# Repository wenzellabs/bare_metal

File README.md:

# bare_metal

**bare metal** is an FPGA development board - the ideal platform to get started with FPGAs and HDL of one or another sort. all open source.

you can buy bare_metal <a href="https://lectronz.com/products/bare_metal"> over at my little lectronz shop</a>.

bare_metal, the opensource FPGA development board:

- five user buttons: OK, left, right, up, down
- large 16x8 SPI-addressable RGB LEDs display
- extensible through a PMOD interface
- comes with a battery for many hours of runtime
- extensive power management, monitoring and battery protection in HW
- allows for CPU-less designs or soft-core CPUs
- get into FPGAs with the **yosys** and **nextpnr** all open source toolchains
- program in python/amarant, verilog, spade or others
- comes with a stand
- three bright white LEDs as simple debug or flashlight
- usable as name tag, comes with a lace
- comes with a bootloader as 1st of four bitstreams
- can host up to 3 user bitstreams
- 16MBytes flash in total (1 bitstream takes < 128kBytes)
- 8MBytes RAM in total
- transputer research platform, as 3 user bitstreams can "boot" each other, see `bootloader` below
- hacky but feasible: more that 3 user bitstreams (hundreds)

## tech bits

### schematic

see the [hardware](hardware/) directory. find [the schematics](hardware/bare_metal_schematic.pdf), the KiCad sources and [some](hardware/bare_metal_front.png) [nice](hardware/bare_metal_back.png) [renderings](hardware/bare_metal_3d.png).

### memory

- 16MBytes SPI flash (W25Q128JVSIQ) this is where the FPGA boots from and user storage such as text, fonts, images, sounds, video, etc.
- 8MBytes SPI PSRAM (LY68L6400) far all of your extensive memory needs

here's a memory map of the SPI flash:

```
# 0x000_0000 - 0x000_009f =160b, multiboot header, slot table
# 0x000_00a0 - 0x001_efff ~124kB, slot 0, bare_metal_bootloader
# 0x001_f000 - 0x001_ffff =4kB, bootmetadata
# 0x002_0000 - 0x003_ffff =128kB, slot 1, user bitstream, hackerstacker_demo by default
# 0x004_0000 - 0x005_ffff =128kB, slot 2, another bitstream, transputers anyone?
# 0x006_0000 - 0x007_ffff ~128kB, slot 3, yab, hooray for transputers!
# 0x008_0000 - 0x100_0000 ~15.5MB, user data, images, fonts, text, sounds, videos etc
```
```
# in hackerstacker_demo, we reserve the first 512 KB for bootloader and bitstreams,
# and use the rest for user data:
# 0x008_0000 - 0x008_ffff = 64 kB, font data
# 0x009_0000 - 0x009_ffff = 64 kB, game data
# 0x00a_0000 - 0x00a_ffff = 64 kB, nick names
# 0x00b_0000 - 0x0ff_ffff = ~15.3MB images, video
```

### bootloader

the bootloader is always started after power up or reset. it lives in slot0 of the four default bitstream slots.

the bootloader is forked from https://github.com/tinyfpga/TinyFPGA-Bootloader which looks unmaintained nowadays. we forked, and implement our bootloader and the `tinyprog` flashing tool at https://codeberg.org/wenzellabs/bare_metal_bootloader

```

                   [-----------][----------][----------]
                   [ user bit- ][ user bit-][ user bit-]
                   [ stream 1  ][ stream 2 ][ stream 3 ]
                   [           ][          ][          ]
                   [===========][==========][==========]
                   [-----------------------------------]
                   [    USB-bootloader bitstream 0     ]
                   [===================================]
               [-------------------------------------------]
               [ iCE40-up5k-sg48 FPGA, 5k LCs, DSP fn()s   ]
               [===========================================]
[-----]    [----------------------------------------------------]    [---------------]
[ USB ]----[ bare_metal, buttons, batt., LEDs, RGB-display, PMOD]----[PMOD extensions]
[=====]    [====================================================]    [===============]

```

the bootloader animates the three white LEDs `index`, `middle` and `pinky`. if the bootloader detects a host PC (if it gets USB enumerated) it stays in the bootloader and creates a cdc_acm /dev/ttyACM0 that can be used in conjunction with tinyprog to flash user bitstreams into slot1, slot2 or slot3, or any other flash content.

if no host PC is detected the bootloader "jumps" to the user bitstream in slot1.

**stay in bootloader** although there's no host PC:

- press btn_**down** while powerup/reset.

jump to **slot1** user bitstrem although we're connected to a host PC:

- press btn_**ok** while powerup/reset.

jump to **slot2** user bitstrem although we're connected to a host PC:

- press btn_**left** while powerup/reset.

jump to **slot3** user bitstrem although we're connected to a host PC:

- press btn_**right** while powerup/reset.

### examples

#### hackerstacker_demo

by default the first user bitstream in slot1 is hackerstacker_demo, that has various modes, which can be advanced by a long btn_ok press.

modes:

- hackerstacker game, control: btn_ok
- scroll user text. control: switch text: btn_ok, brightness: btn_up, btn_down, scroll-mode: btn_left, font: btn-right
- skating images. control: btn_ok
- various static patterns, rainbow, trans flag, checker board. control: btn_ok
- various animated patterns, rainbow, trans flag. control: btn_ok

the texts, fonts and images live in the SPI flash aside from the bitstream, so they can be replaced or extended without re-synthesizing the bitstream.
see [the hackerstacker_demo directory](firmware/examples/amaranth/hackerstacker_demo) and there the make targets
```
make flash-nick # see nick.txt first!
make flash-font
make flash-image # see image.txt first!
```

#### julia

reach it by pressing btn_left while powerup/reset.

by default the second user bitstream in slot2 is julia. it renders a julia set, and loops:

- pan to a random position
- zoom in until the entropy is too low
- zoom out again

the up/down/left/right control the complex coordinate C of the julia set being rendered.

the OK button changes the palette.

#### psram_probe

reach it by pressing btn_right while powerup/reset.

for now the default third user bitstream in slot3 is psram_probe, just a production PSRAM test. lights up one LED in green per pass.

I hope to get some small spade demo, looking at you @TheZoq2.

### power

#### battery

a PS5 controller compatible battery similar to SNYHR37. 2500 mAh, 1S.
the little plasic box is a nice feature to protect the pouch cell from stabbing you and vice versa.

#### USB-C

there's a current limit of 500mA in place. no USB-PD, just 5V.

the data pins are usable and available for creating any USB2 devices. the board has no dedicated USB-HW (aside from ESD protection) but anything can be implemented in the FPGA, just as the bootloader does. related pins:

```
# USB
set_io -nowarn usbp         42    # IOT_51a  - USB D+
set_io -nowarn usbn         38    # IOT_50b  - USB D-
set_io -nowarn usb_det      37    # IOT_36b  - USB_DET, active-high enables 1k5 pull-up on D+
```

#### battery protection

we turn the screen off at around 3V battery voltage to notify the user that she needs a power up. there's also a red `charge me` LED that indicates this state.
at 2.5V a hard battery protection kicks in, and everything is switched off, until charging via USB-C again.

there's also a overvoltage and overcurrent protection and thermal monitoring in place.

#### the ring of power

bare_metal wears a little ring at it's pinky, the `ring of power`.
here all various important voltages are accessible:

- 1 GND
- 2 VBUS
- 3 VBAT_MINUS
- 4 BAT_TEMP_SENSE
- 5 VBAT
- 5 3V3
- 6 VCHG
- 7 VMAIN

## the FPGA

it's a **Lattice iCE40 UP5K** in a **SG48** package

- fully supported by yosys and nextpnr
- 5000+ LUTs
- 8 DSP blocks (MULT16 with ACC32)
- 1024kBits SPRAM in 4 blocks
- 120kBits EBR memory in 30 blocks
- 2 hard I2C blocks
- 2 hard SPI blocks

## pinout

it's all in the examples and printed on the stand, but for completenes here's a PCF:

```
# bare_metal
# iCE40UP5K SG48 (QFN 48)

# this is a complete bare_metal pin definition
# you may use for your designs

# 12 MHz crystal oscillator (dedicated clock pad)
set_io -nowarn clk_12M      35    # IOT_46b_G0

# USB
set_io -nowarn usbp         42    # IOT_51a  - USB D+
set_io -nowarn usbn         38    # IOT_50b  - USB D-
set_io -nowarn usb_det      37    # IOT_36b  - USB_DET, active-high enables 1k5 pull-up on D+

# buttons
set_io -nowarn btn_ok       23    # IOT_37a
set_io -nowarn btn_up       45    # IOB_5b
set_io -nowarn btn_down     11    # IOB_20a
set_io -nowarn btn_left     44    # IOB_3b_G6
set_io -nowarn btn_right    10    # IOB_18a

# LED indicators - three white LEDs, low active
set_io -nowarn led_index    39    # white_index
set_io -nowarn led_middle   40    # white_middle
set_io -nowarn led_pinky    41    # white_pinky

# SPI configuration flash
set_io -nowarn spi_mosi     14    # IOB_32a - SPI_SO, MOSI
set_io -nowarn spi_miso     17    # IOB_33b - SPI_SI, MISO
set_io -nowarn spi_clk      15    # IOB_34a - SPI_SCK
set_io -nowarn spi_csn_flash 16   # IOB_35b - SPI_CSn_FLASH
set_io -nowarn spi_wp       18    # IOB_31b - SPI_WPn
set_io -nowarn spi_hold     19    # IOB_29b - SPI_HOLDn

# SPI PSRAM, same as above, just CSn
set_io -nowarn spi_csn_ram   6    # IOB_13b - SPI_CSn_RAM

# SK9822 / APA102-compatible LED matrix (128 LEDs, 16x8)
set_io -nowarn led_di        4    # IOB_8a
set_io -nowarn led_ci        3    # IOB_9b

# LED matrix power enable
set_io -nowarn led_power_on 46    # IOB_0a

# PMOD interface - mind the special pin numbering of PMOD interfaces!
set_io -nowarn -pullup yes pmod_a_n     27   # PMOD pin 1
set_io -nowarn -pullup yes pmod_a_p     26   # PMOD pin 7
set_io -nowarn -pullup yes pmod_2       25   # PMOD pin 2
set_io -nowarn -pullup yes pmod_8       28   # PMOD pin 8
set_io -nowarn -pullup yes pmod_b_p     32   # PMOD pin 3
set_io -nowarn -pullup yes pmod_b_n     31   # PMOD pin 9
set_io -nowarn -pullup yes pmod_4       13   # PMOD pin 4
set_io -nowarn -pullup yes pmod_10      12   # PMOD pin 10

```

## stand

the stand can serve multiple purposes

it conveniently lists all PMOD and all other pins.

use it to display the bare_metal board, by sliding the two slots into each other.

or when hanging the bare_metal around your neck (or elsewhere) you can hang the stand into the bottom holes, the stand then mimicks a sleeve.

## what's included?

- bare_metal main board
- rugged lace, detachable
- two soft plastic rings to hang bare_metal and its stand together
- the bare_metal stand PCB
- the 1S LiPo battery
- double sided adhesive tape to mount the battery on the bare_metal main board

## where to get?

bare_metal is available through <a href="https://lectronz.com/products/bare_metal">my little lectronz shop</a>.

## license

Copyright (c) 2026 m. wenzel, wenzellabs

Unless otherwise stated, the hardware designs, firmware source code,
and documentation in this repository are licensed under:

Creative Commons Attribution-NonCommercial-ShareAlike 4.0 International
(CC BY-NC-SA 4.0)

https://creativecommons.org/licenses/by-nc-sa/4.0/

Commercial use, including commercial manufacture, sale, or distribution
of products based on these materials, is not permitted without
separate permission from the copyright holder.

see LICENSE.txt

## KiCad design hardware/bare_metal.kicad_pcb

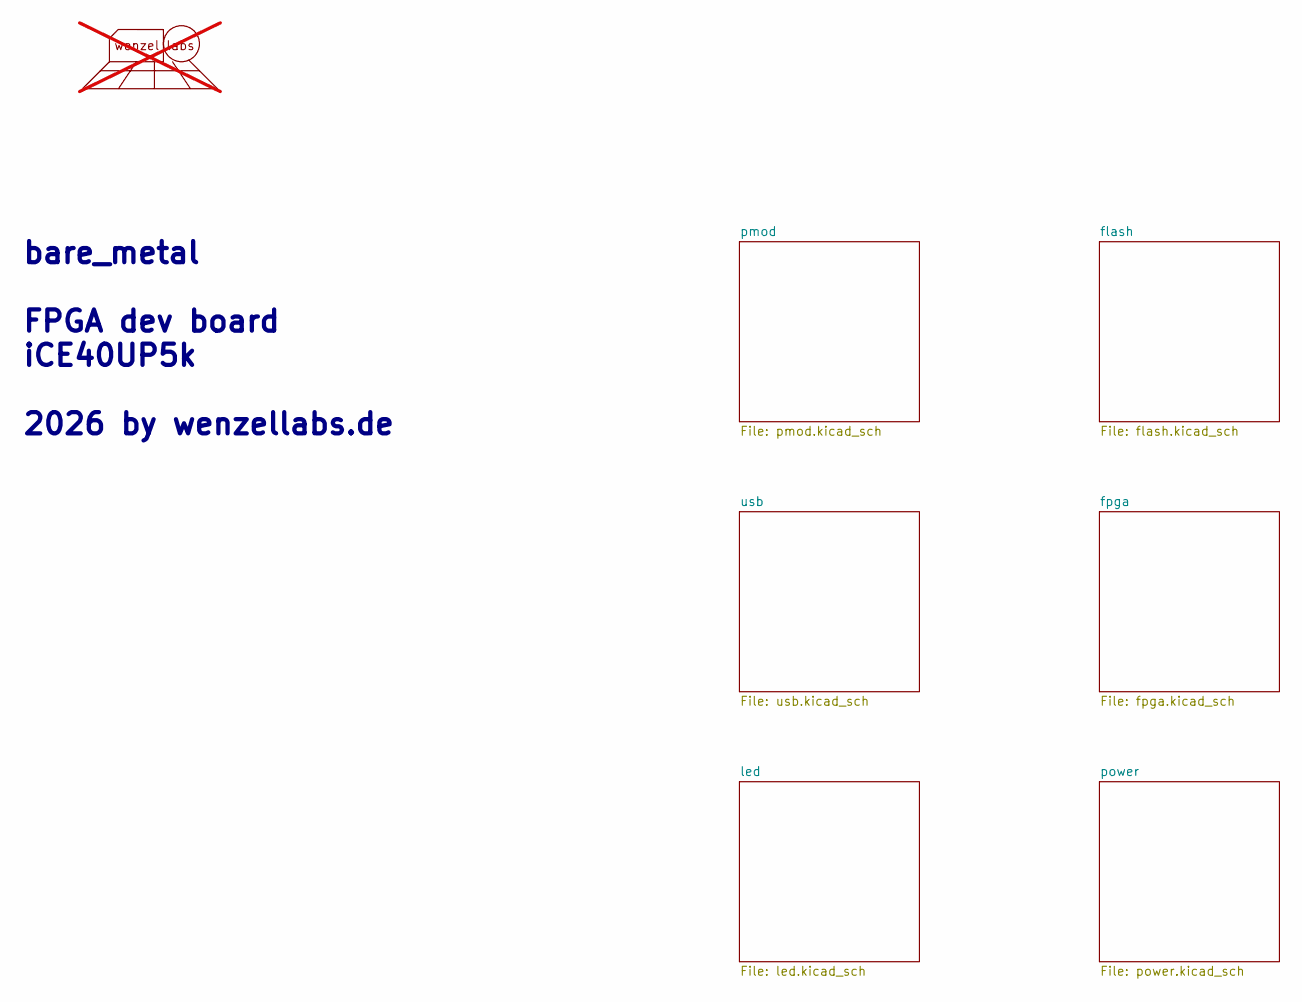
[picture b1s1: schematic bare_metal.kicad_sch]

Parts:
L101: Logo wenzellabs; wenzellabs_logo_v1_13x6; not fitted

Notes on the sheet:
bare_metal FPGA dev board iCE40UP5k 2026 by wenzellabs.de

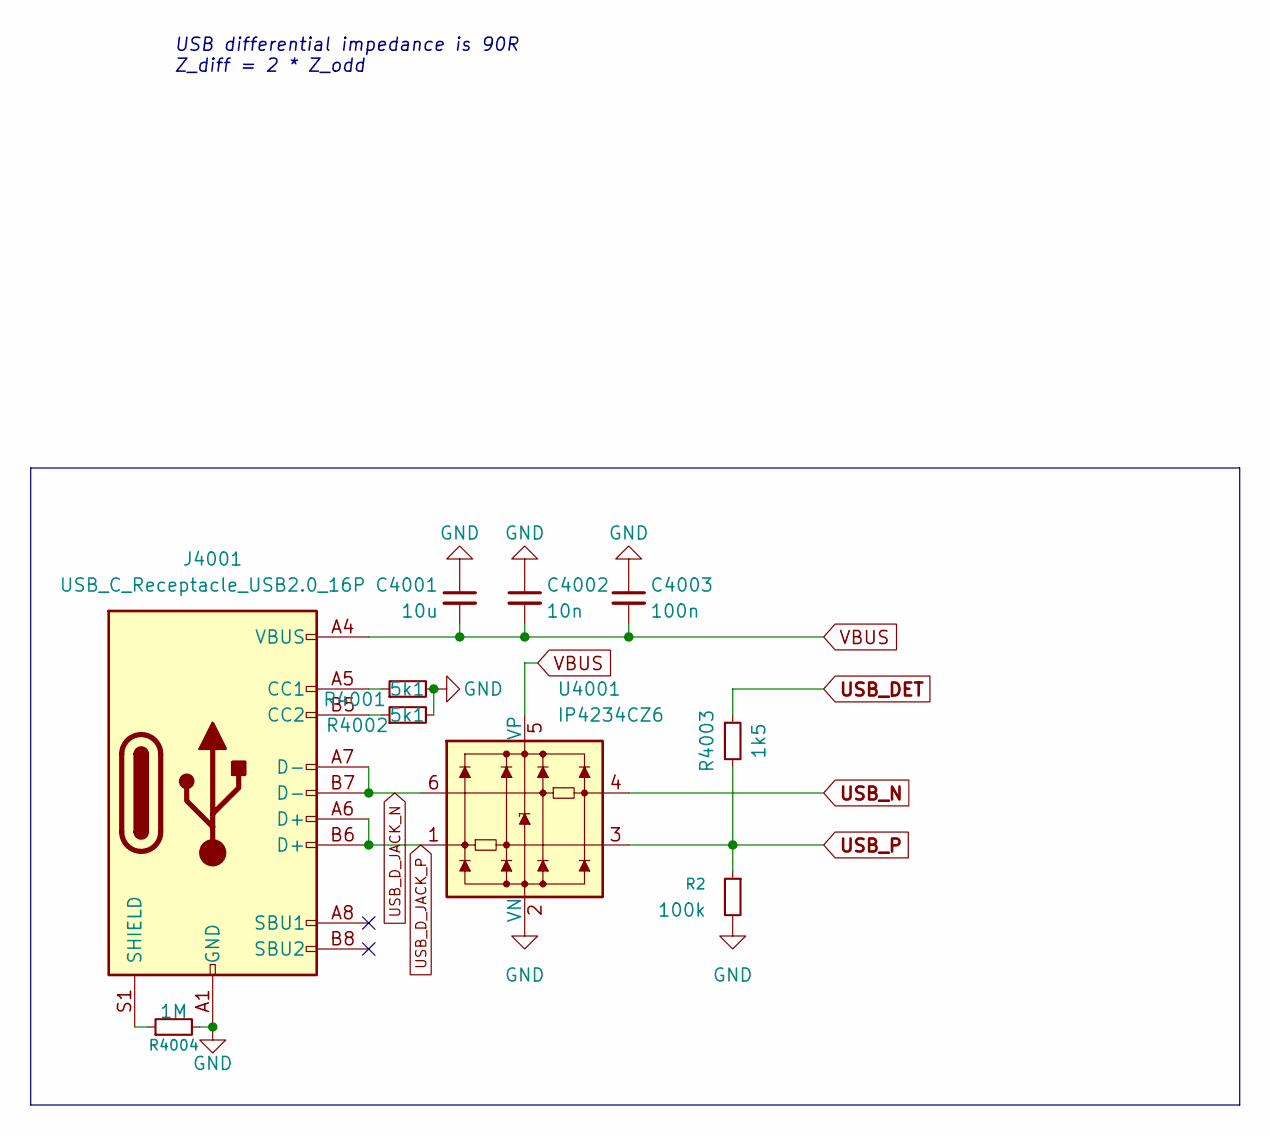
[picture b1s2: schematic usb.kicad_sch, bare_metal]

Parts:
C4001: 10u; C_0603_1608Metric
C4002: 10n; C_0402_1005Metric
C4003: 100n; C_0402_1005Metric
J4001: USB_C_Receptacle_USB2.0_16P; USB_C_Receptacle_GCT_USB4800-03-A_16P_TopMnt_Horizontal
R2: 100k; R_0402_1005Metric
R4001, R4002: 5k1; R_0402_1005Metric
R4003: 1k5; R_0402_1005Metric
R4004: 1M; R_2512_6332Metric
U4001: IP4234CZ6; SC-74-6_1.55x2.9mm_P0.95mm

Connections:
GND: C4001.1, C4002.1, C4003.1, J4001.A1 (GND), J4001.A12 (GND), J4001.B1 (GND), J4001.B12 (GND), R2.2, R4001.2, R4002.2, R4004.2, U4001.2 (VN); also elsewhere on the board
unnamed: J4001.A5 (CC1), R4001.1
unnamed: J4001.B5 (CC2), R4002.1
unnamed: J4001.S1 (SHIELD), R4004.1
USB_DET: R4003.1; also elsewhere on the board
USB_D_JACK_N: J4001.A7 (D-), J4001.B7 (D-), U4001.6
USB_D_JACK_P: J4001.A6 (D+), J4001.B6 (D+), U4001.1
USB_N: U4001.4; also elsewhere on the board
USB_P: R2.1, R4003.2, U4001.3; also elsewhere on the board
VBUS: C4001.2, C4002.2, C4003.2, J4001.A4 (VBUS), J4001.A9 (VBUS), J4001.B4 (VBUS), J4001.B9 (VBUS), U4001.5 (VP); also elsewhere on the board

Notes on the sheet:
USB differential impedance is 90R Z_diff = 2 * Z_odd

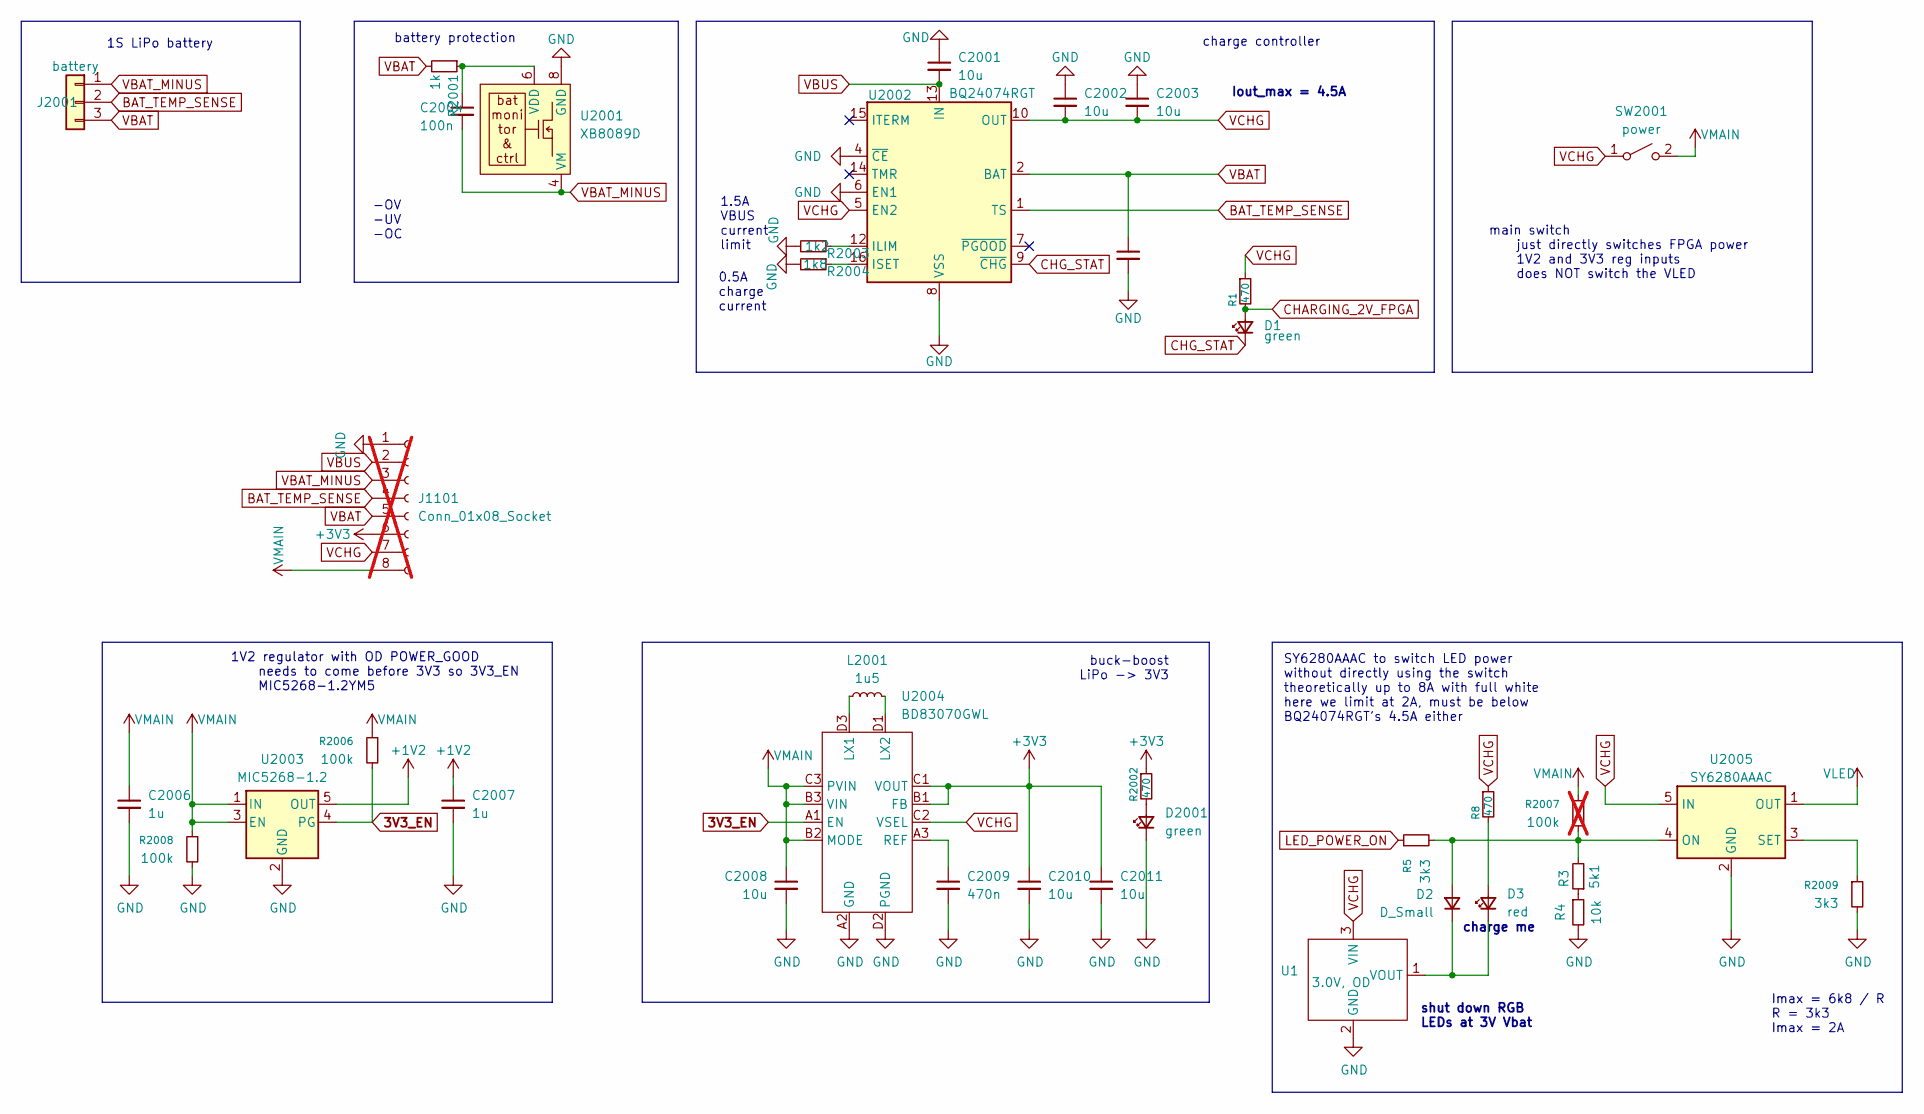
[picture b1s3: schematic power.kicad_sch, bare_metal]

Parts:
C2001, C2002, C2003, C2005, C2008, C2010, C2011: 10u; C_0603_1608Metric
C2004: 100n; C_0402_1005Metric
C2006, C2007: 1u; C_0402_1005Metric
C2009: 470n; C_0402_1005Metric
D1, D2001: green; LED_0805_2012Metric
D2: D_Small; D_SOD-123
D3: red; LED_0805_2012Metric
J1101: Conn_01x08_Socket; PinSocket_1x08_P2.54mm_Vertical; not fitted
J2001: battery; JST_ZH_S3B-ZR-SM4A-TF_1x03-1MP_P1.50mm_Horizontal
L2001: 1u5; L_1008_2520Metric
R1, R8, R2002: 470; R_0402_1005Metric
R3: 5k1; R_0402_1005Metric
R4: 10k; R_0402_1005Metric
R5, R2009: 3k3; R_0402_1005Metric
R2001: 1k; R_0402_1005Metric
R2003: 1k2; R_0402_1005Metric
R2004: 1k8; R_0402_1005Metric
R2006, R2008: 100k; R_0402_1005Metric
R2007: 100k; R_0402_1005Metric; not fitted
SW2001: power; diptronics_switch_SS3-CM
U1: 3.0V, OD; SOT-23-3
U2001: XB8089D; SOIC-8-1EP_3.9x4.9mm_P1.27mm_EP2.62x3.51mm_ThermalVias
U2002: BQ24074RGT; VQFN-16-1EP_3x3mm_P0.5mm_EP1.6x1.6mm
U2003: MIC5268-1.2; SOT-23-5
U2004: BD83070GWL; UCSP50L1C
U2005: SY6280AAAC; SOT-23-5

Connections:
3V3_EN: R2006.2, U2003.4 (PG), U2004.A1 (EN)
+1V2: C2007.1, U2003.5 (OUT); also elsewhere on the board
+3V3: C2010.1, C2011.1, J1101.6, R2002.1, U2004.B1 (FB), U2004.C1 (VOUT); also elsewhere on the board
BAT_TEMP_SENSE: J1101.4, J2001.2, U2002.1 (TS)
CHARGING_2V_FPGA: D1.2 (A), R1.2; also elsewhere on the board
CHG_STAT: D1.1 (K), U2002.9 (~CHG)
GND: C2001.1, C2002.1, C2003.1, C2005.2, C2006.2, C2007.2, C2008.2, C2009.2, C2010.2, C2011.2, D2001.1 (K), J1101.1, R4.2, R2003.2, R2004.2, R2008.2, R2009.2, U1.2 (GND), U2001.5 (GND), U2001.7 (GND), U2001.8 (GND), U2001.9 (GND), U2002.4 (~CE), U2002.6 (EN1), U2002.8 (VSS), U2002.17 (VSS), U2003.2 (GND), U2004.A2 (GND), U2004.D2 (PGND), U2005.2 (GND); also elsewhere on the board
LED_POWER_ON: R5.1; also elsewhere on the board
unnamed: D2.2 (A), R3.2, R5.2, R2007.2, U2005.4 (ON)
unnamed: D2.1 (K), D3.1 (K), U1.1 (VOUT)
unnamed: D3.2 (A), R8.2
unnamed: D2001.2 (A), R2002.2
unnamed: R3.1, R4.1
unnamed: C2004.1, R2001.1, U2001.6 (VDD)
unnamed: R2003.1, U2002.12 (ILIM)
unnamed: R2004.1, U2002.16 (ISET)
unnamed: L2001.1, U2004.D3 (LX1)
unnamed: L2001.2, U2004.D1 (LX2)
unnamed: C2009.1, U2004.A3 (REF)
unnamed: R2009.1, U2005.3 (SET)
VBAT: C2005.1, J1101.5, J2001.3, R2001.2, U2002.2 (BAT), U2002.3 (BAT)
VBAT_MINUS: C2004.2, J1101.3, J2001.1, U2001.1 (VM), U2001.2 (VM), U2001.3 (VM), U2001.4 (VM)
VBUS: C2001.2, J1101.2, U2002.13 (IN); also elsewhere on the board
VCHG: C2002.2, C2003.2, J1101.7, R1.1, R8.1, SW2001.1 (A), U1.3 (VIN), U2002.5 (EN2), U2002.10 (OUT), U2002.11 (OUT), U2004.C2 (VSEL), U2005.5 (IN)
VLED: U2005.1 (OUT); also elsewhere on the board
VMAIN: C2006.1, C2008.1, J1101.8, R2006.1, R2007.1, R2008.1, SW2001.2 (B), U2003.1 (IN), U2003.3 (EN), U2004.B2 (MODE), U2004.B3 (VIN), U2004.C3 (PVIN)

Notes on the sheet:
1S LiPo battery
main switch just directly switches FPGA power 1V2 and 3V3 reg inputs does NOT switch the VLED
battery protection
SY6280AAAC to switch LED power without directly using the switch theoretically up to 8A with full white here we limit at 2A, must be below BQ24074RGT's 4.5A either
charge controller
Imax = 6k8 / R R = 3k3 Imax = 2A
0.5A charge current
1V2 regulator with OD POWER_GOOD needs to come before 3V3 so 3V3_EN MIC5268-1.2YM5
buck-boost LiPo -> 3V3
Iout_max = 4.5A
-OV -UV -OC
charge me
shut down RGB LEDs at 3V Vbat
1.5A VBUS current limit

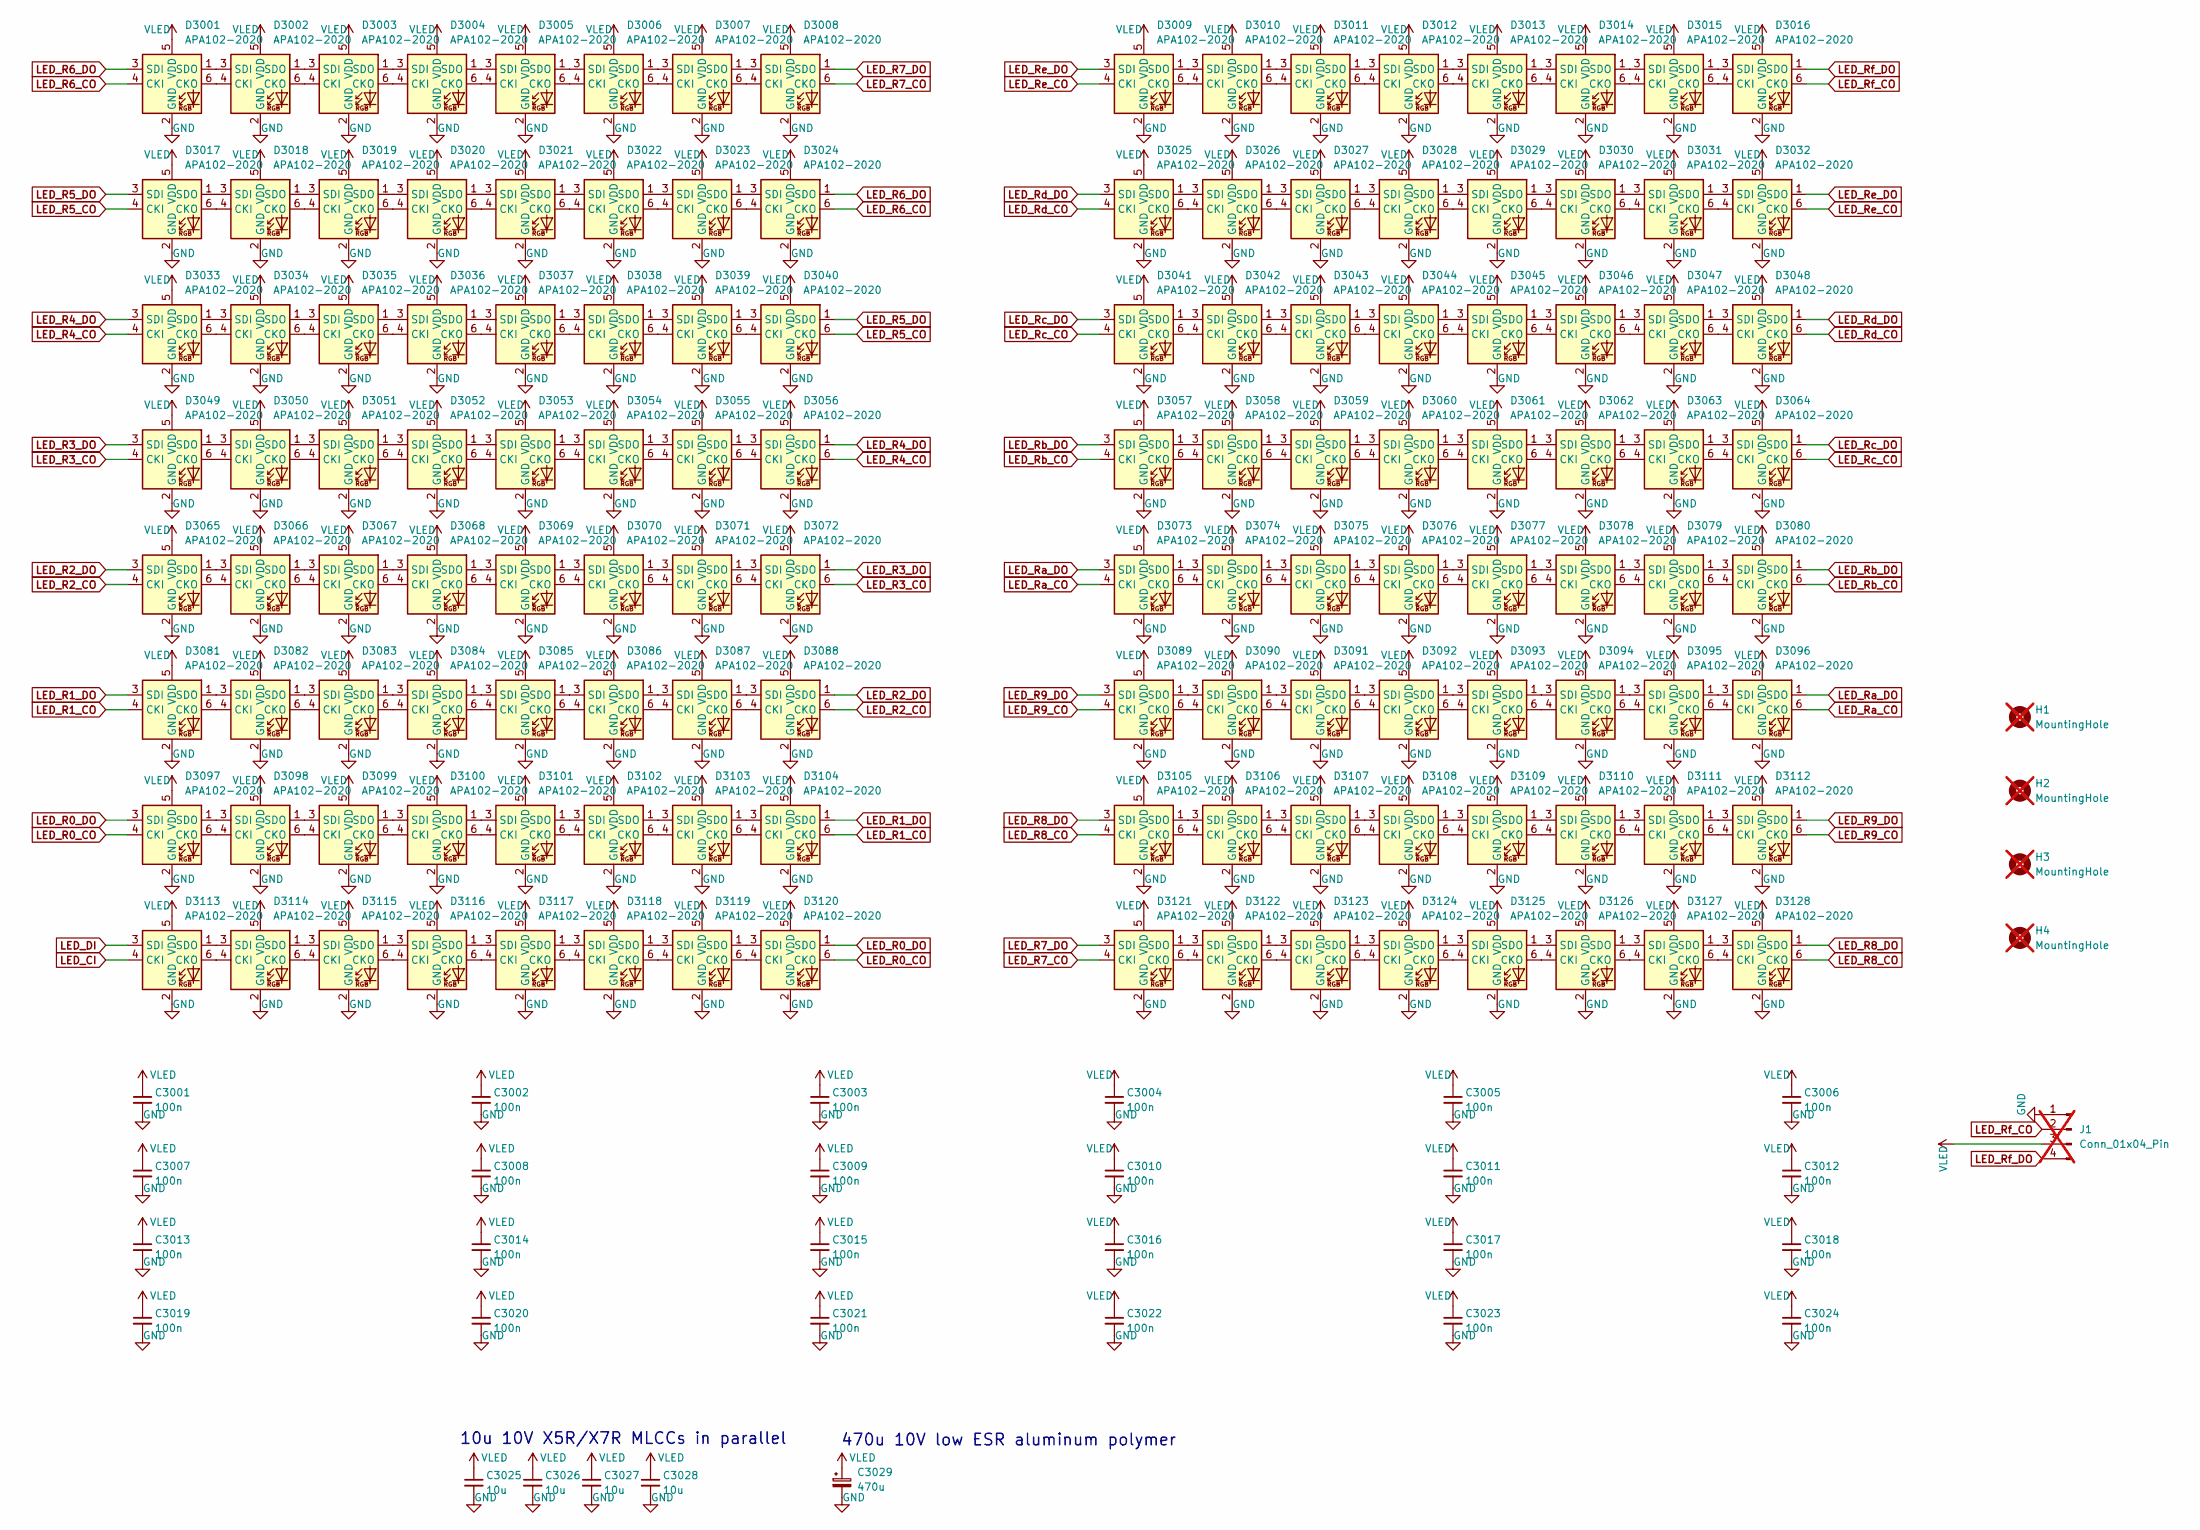
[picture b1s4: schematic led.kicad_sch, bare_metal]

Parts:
C3001, C3002, C3003, C3004, C3005, C3006, C3007, C3008, C3009, C3010, C3011, C3012, C3013, C3014, C3015, C3016, C3017, C3018, C3019, C3020, C3021, C3022, C3023, C3024: 100n; C_0402_1005Metric
C3025, C3026, C3027, C3028: 10u; C_0603_1608Metric
C3029: 470u; CP_Elec_6.3x7.7
D3001, D3002, D3003, D3004, D3005, D3006, D3007, D3008, D3009, D3010, D3011, D3012, D3013, D3014, D3015, D3016, D3017, D3018, D3019, D3020, D3021, D3022, D3023, D3024, D3025, D3026, D3027, D3028, D3029, D3030, D3031, D3032, D3033, D3034, D3035, D3036, D3037, D3038, D3039, D3040, D3041, D3042, D3043, D3044, D3045, D3046, D3047, D3048, D3049, D3050, D3051, D3052, D3053, D3054, D3055, D3056, D3057, D3058, D3059, D3060, D3061, D3062, D3063, D3064, D3065, D3066, D3067, D3068, D3069, D3070, D3071, D3072, D3073, D3074, D3075, D3076, D3077, D3078, D3079, D3080, D3081, D3082, D3083, D3084, D3085, D3086, D3087, D3088, D3089, D3090, D3091, D3092, D3093, D3094, D3095, D3096, D3097, D3098, D3099, D3100, D3101, D3102, D3103, D3104, D3105, D3106, D3107, D3108, D3109, D3110, D3111, D3112, D3113, D3114, D3115, D3116, D3117, D3118, D3119, D3120, D3121, D3122, D3123, D3124, D3125, D3126, D3127, D3128: APA102-2020; SK9822-EC20
H1, H2, H3, H4: MountingHole; MountingHole_2mm; not fitted
J1: Conn_01x04_Pin; SMD_pads_01x04; not fitted

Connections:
GND: C3001.2, C3002.2, C3003.2, C3004.2, C3005.2, C3006.2, C3007.2, C3008.2, C3009.2, C3010.2, C3011.2, C3012.2, C3013.2, C3014.2, C3015.2, C3016.2, C3017.2, C3018.2, C3019.2, C3020.2, C3021.2, C3022.2, C3023.2, C3024.2, C3025.2, C3026.2, C3027.2, C3028.2, C3029.2, D3001.2 (GND), D3002.2 (GND), D3003.2 (GND), D3004.2 (GND), D3005.2 (GND), D3006.2 (GND), D3007.2 (GND), D3008.2 (GND), D3009.2 (GND), D3010.2 (GND), D3011.2 (GND), D3012.2 (GND), D3013.2 (GND), D3014.2 (GND), D3015.2 (GND), D3016.2 (GND), D3017.2 (GND), D3018.2 (GND), D3019.2 (GND), D3020.2 (GND), D3021.2 (GND), D3022.2 (GND), D3023.2 (GND), D3024.2 (GND), D3025.2 (GND), D3026.2 (GND), D3027.2 (GND), D3028.2 (GND), D3029.2 (GND), D3030.2 (GND), D3031.2 (GND), D3032.2 (GND), D3033.2 (GND), D3034.2 (GND), D3035.2 (GND), D3036.2 (GND), D3037.2 (GND), D3038.2 (GND), D3039.2 (GND), D3040.2 (GND), D3041.2 (GND), D3042.2 (GND), D3043.2 (GND), D3044.2 (GND), D3045.2 (GND), D3046.2 (GND), D3047.2 (GND), D3048.2 (GND), D3049.2 (GND), D3050.2 (GND), D3051.2 (GND), D3052.2 (GND), D3053.2 (GND), D3054.2 (GND), D3055.2 (GND), D3056.2 (GND), D3057.2 (GND), D3058.2 (GND), D3059.2 (GND), D3060.2 (GND), D3061.2 (GND), D3062.2 (GND), D3063.2 (GND), D3064.2 (GND), D3065.2 (GND), D3066.2 (GND), D3067.2 (GND), D3068.2 (GND), D3069.2 (GND), D3070.2 (GND), D3071.2 (GND), D3072.2 (GND), D3073.2 (GND), D3074.2 (GND), D3075.2 (GND), D3076.2 (GND), D3077.2 (GND), D3078.2 (GND), D3079.2 (GND), D3080.2 (GND), D3081.2 (GND), D3082.2 (GND), D3083.2 (GND), D3084.2 (GND), D3085.2 (GND), D3086.2 (GND), D3087.2 (GND), D3088.2 (GND), D3089.2 (GND), D3090.2 (GND), D3091.2 (GND), D3092.2 (GND), D3093.2 (GND), D3094.2 (GND), D3095.2 (GND), D3096.2 (GND), D3097.2 (GND), D3098.2 (GND), D3099.2 (GND), D3100.2 (GND), D3101.2 (GND), D3102.2 (GND), D3103.2 (GND), D3104.2 (GND), D3105.2 (GND), D3106.2 (GND), D3107.2 (GND), D3108.2 (GND), D3109.2 (GND), D3110.2 (GND), D3111.2 (GND), D3112.2 (GND), D3113.2 (GND), D3114.2 (GND), D3115.2 (GND), D3116.2 (GND), D3117.2 (GND), D3118.2 (GND), D3119.2 (GND), D3120.2 (GND), D3121.2 (GND), D3122.2 (GND), D3123.2 (GND), D3124.2 (GND), D3125.2 (GND), D3126.2 (GND), D3127.2 (GND), D3128.2 (GND), J1.1; also elsewhere on the board
LED_CI: D3113.4 (CKI); also elsewhere on the board
LED_DI: D3113.3 (SDI); also elsewhere on the board
LED_R0_CO: D3097.4 (CKI), D3120.6 (CKO)
LED_R0_DO: D3097.3 (SDI), D3120.1 (SDO)
LED_R1_CO: D3081.4 (CKI), D3104.6 (CKO)
LED_R1_DO: D3081.3 (SDI), D3104.1 (SDO)
LED_R2_CO: D3065.4 (CKI), D3088.6 (CKO)
LED_R2_DO: D3065.3 (SDI), D3088.1 (SDO)
LED_R3_CO: D3049.4 (CKI), D3072.6 (CKO)
LED_R3_DO: D3049.3 (SDI), D3072.1 (SDO)
LED_R4_CO: D3033.4 (CKI), D3056.6 (CKO)
LED_R4_DO: D3033.3 (SDI), D3056.1 (SDO)
LED_R5_CO: D3017.4 (CKI), D3040.6 (CKO)
LED_R5_DO: D3017.3 (SDI), D3040.1 (SDO)
LED_R6_CO: D3001.4 (CKI), D3024.6 (CKO)
LED_R6_DO: D3001.3 (SDI), D3024.1 (SDO)
LED_R7_CO: D3008.6 (CKO), D3121.4 (CKI)
LED_R7_DO: D3008.1 (SDO), D3121.3 (SDI)
LED_R8_CO: D3105.4 (CKI), D3128.6 (CKO)
LED_R8_DO: D3105.3 (SDI), D3128.1 (SDO)
LED_R9_CO: D3089.4 (CKI), D3112.6 (CKO)
LED_R9_DO: D3089.3 (SDI), D3112.1 (SDO)
LED_Ra_CO: D3073.4 (CKI), D3096.6 (CKO)
LED_Ra_DO: D3073.3 (SDI), D3096.1 (SDO)
LED_Rb_CO: D3057.4 (CKI), D3080.6 (CKO)
LED_Rb_DO: D3057.3 (SDI), D3080.1 (SDO)
LED_Rc_CO: D3041.4 (CKI), D3064.6 (CKO)
LED_Rc_DO: D3041.3 (SDI), D3064.1 (SDO)
LED_Rd_CO: D3025.4 (CKI), D3048.6 (CKO)
LED_Rd_DO: D3025.3 (SDI), D3048.1 (SDO)
LED_Re_CO: D3009.4 (CKI), D3032.6 (CKO)
LED_Re_DO: D3009.3 (SDI), D3032.1 (SDO)
LED_Rf_CO: D3016.6 (CKO), J1.2
LED_Rf_DO: D3016.1 (SDO), J1.4
unnamed: D3001.6 (CKO), D3002.4 (CKI)
unnamed: D3001.1 (SDO), D3002.3 (SDI)
unnamed: D3002.6 (CKO), D3003.4 (CKI)
unnamed: D3002.1 (SDO), D3003.3 (SDI)
unnamed: D3003.6 (CKO), D3004.4 (CKI)
unnamed: D3003.1 (SDO), D3004.3 (SDI)
unnamed: D3004.6 (CKO), D3005.4 (CKI)
unnamed: D3004.1 (SDO), D3005.3 (SDI)
unnamed: D3005.6 (CKO), D3006.4 (CKI)
unnamed: D3005.1 (SDO), D3006.3 (SDI)
unnamed: D3006.6 (CKO), D3007.4 (CKI)
unnamed: D3006.1 (SDO), D3007.3 (SDI)
unnamed: D3007.6 (CKO), D3008.4 (CKI)
unnamed: D3007.1 (SDO), D3008.3 (SDI)
unnamed: D3009.6 (CKO), D3010.4 (CKI)
unnamed: D3009.1 (SDO), D3010.3 (SDI)
unnamed: D3010.6 (CKO), D3011.4 (CKI)
unnamed: D3010.1 (SDO), D3011.3 (SDI)
unnamed: D3011.6 (CKO), D3012.4 (CKI)
unnamed: D3011.1 (SDO), D3012.3 (SDI)
unnamed: D3012.6 (CKO), D3013.4 (CKI)
unnamed: D3012.1 (SDO), D3013.3 (SDI)
unnamed: D3013.6 (CKO), D3014.4 (CKI)
unnamed: D3013.1 (SDO), D3014.3 (SDI)
unnamed: D3014.6 (CKO), D3015.4 (CKI)
unnamed: D3014.1 (SDO), D3015.3 (SDI)
unnamed: D3015.6 (CKO), D3016.4 (CKI)
unnamed: D3015.1 (SDO), D3016.3 (SDI)
unnamed: D3017.6 (CKO), D3018.4 (CKI)
unnamed: D3017.1 (SDO), D3018.3 (SDI)
unnamed: D3018.6 (CKO), D3019.4 (CKI)
unnamed: D3018.1 (SDO), D3019.3 (SDI)
unnamed: D3019.6 (CKO), D3020.4 (CKI)
unnamed: D3019.1 (SDO), D3020.3 (SDI)
unnamed: D3020.6 (CKO), D3021.4 (CKI)
unnamed: D3020.1 (SDO), D3021.3 (SDI)
unnamed: D3021.6 (CKO), D3022.4 (CKI)
unnamed: D3021.1 (SDO), D3022.3 (SDI)
unnamed: D3022.6 (CKO), D3023.4 (CKI)
unnamed: D3022.1 (SDO), D3023.3 (SDI)
unnamed: D3023.6 (CKO), D3024.4 (CKI)
unnamed: D3023.1 (SDO), D3024.3 (SDI)
unnamed: D3025.6 (CKO), D3026.4 (CKI)
unnamed: D3025.1 (SDO), D3026.3 (SDI)
unnamed: D3026.6 (CKO), D3027.4 (CKI)
unnamed: D3026.1 (SDO), D3027.3 (SDI)
unnamed: D3027.6 (CKO), D3028.4 (CKI)
unnamed: D3027.1 (SDO), D3028.3 (SDI)
unnamed: D3028.6 (CKO), D3029.4 (CKI)
unnamed: D3028.1 (SDO), D3029.3 (SDI)
unnamed: D3029.6 (CKO), D3030.4 (CKI)
unnamed: D3029.1 (SDO), D3030.3 (SDI)
unnamed: D3030.6 (CKO), D3031.4 (CKI)
unnamed: D3030.1 (SDO), D3031.3 (SDI)
unnamed: D3031.6 (CKO), D3032.4 (CKI)
unnamed: D3031.1 (SDO), D3032.3 (SDI)
unnamed: D3033.6 (CKO), D3034.4 (CKI)
unnamed: D3033.1 (SDO), D3034.3 (SDI)
unnamed: D3034.6 (CKO), D3035.4 (CKI)
unnamed: D3034.1 (SDO), D3035.3 (SDI)
unnamed: D3035.6 (CKO), D3036.4 (CKI)
unnamed: D3035.1 (SDO), D3036.3 (SDI)
unnamed: D3036.6 (CKO), D3037.4 (CKI)
unnamed: D3036.1 (SDO), D3037.3 (SDI)
unnamed: D3037.6 (CKO), D3038.4 (CKI)
unnamed: D3037.1 (SDO), D3038.3 (SDI)
unnamed: D3038.6 (CKO), D3039.4 (CKI)
unnamed: D3038.1 (SDO), D3039.3 (SDI)
unnamed: D3039.6 (CKO), D3040.4 (CKI)
unnamed: D3039.1 (SDO), D3040.3 (SDI)
unnamed: D3041.6 (CKO), D3042.4 (CKI)
unnamed: D3041.1 (SDO), D3042.3 (SDI)
unnamed: D3042.6 (CKO), D3043.4 (CKI)
unnamed: D3042.1 (SDO), D3043.3 (SDI)
unnamed: D3043.6 (CKO), D3044.4 (CKI)
unnamed: D3043.1 (SDO), D3044.3 (SDI)
unnamed: D3044.6 (CKO), D3045.4 (CKI)
unnamed: D3044.1 (SDO), D3045.3 (SDI)
unnamed: D3045.6 (CKO), D3046.4 (CKI)
unnamed: D3045.1 (SDO), D3046.3 (SDI)
unnamed: D3046.6 (CKO), D3047.4 (CKI)
unnamed: D3046.1 (SDO), D3047.3 (SDI)
unnamed: D3047.6 (CKO), D3048.4 (CKI)
unnamed: D3047.1 (SDO), D3048.3 (SDI)
unnamed: D3049.6 (CKO), D3050.4 (CKI)
unnamed: D3049.1 (SDO), D3050.3 (SDI)
unnamed: D3050.6 (CKO), D3051.4 (CKI)
unnamed: D3050.1 (SDO), D3051.3 (SDI)
unnamed: D3051.6 (CKO), D3052.4 (CKI)
unnamed: D3051.1 (SDO), D3052.3 (SDI)
unnamed: D3052.6 (CKO), D3053.4 (CKI)
unnamed: D3052.1 (SDO), D3053.3 (SDI)
unnamed: D3053.6 (CKO), D3054.4 (CKI)
unnamed: D3053.1 (SDO), D3054.3 (SDI)
unnamed: D3054.6 (CKO), D3055.4 (CKI)
unnamed: D3054.1 (SDO), D3055.3 (SDI)
unnamed: D3055.6 (CKO), D3056.4 (CKI)
unnamed: D3055.1 (SDO), D3056.3 (SDI)
unnamed: D3057.6 (CKO), D3058.4 (CKI)
unnamed: D3057.1 (SDO), D3058.3 (SDI)
unnamed: D3058.6 (CKO), D3059.4 (CKI)
unnamed: D3058.1 (SDO), D3059.3 (SDI)
unnamed: D3059.6 (CKO), D3060.4 (CKI)
unnamed: D3059.1 (SDO), D3060.3 (SDI)
unnamed: D3060.6 (CKO), D3061.4 (CKI)
unnamed: D3060.1 (SDO), D3061.3 (SDI)
unnamed: D3061.6 (CKO), D3062.4 (CKI)
unnamed: D3061.1 (SDO), D3062.3 (SDI)
unnamed: D3062.6 (CKO), D3063.4 (CKI)
unnamed: D3062.1 (SDO), D3063.3 (SDI)
unnamed: D3063.6 (CKO), D3064.4 (CKI)
unnamed: D3063.1 (SDO), D3064.3 (SDI)
unnamed: D3065.6 (CKO), D3066.4 (CKI)
unnamed: D3065.1 (SDO), D3066.3 (SDI)
unnamed: D3066.6 (CKO), D3067.4 (CKI)
unnamed: D3066.1 (SDO), D3067.3 (SDI)
unnamed: D3067.6 (CKO), D3068.4 (CKI)
unnamed: D3067.1 (SDO), D3068.3 (SDI)
unnamed: D3068.6 (CKO), D3069.4 (CKI)
unnamed: D3068.1 (SDO), D3069.3 (SDI)
unnamed: D3069.6 (CKO), D3070.4 (CKI)
unnamed: D3069.1 (SDO), D3070.3 (SDI)
unnamed: D3070.6 (CKO), D3071.4 (CKI)
unnamed: D3070.1 (SDO), D3071.3 (SDI)
unnamed: D3071.6 (CKO), D3072.4 (CKI)
unnamed: D3071.1 (SDO), D3072.3 (SDI)
unnamed: D3073.6 (CKO), D3074.4 (CKI)
unnamed: D3073.1 (SDO), D3074.3 (SDI)
unnamed: D3074.6 (CKO), D3075.4 (CKI)
unnamed: D3074.1 (SDO), D3075.3 (SDI)
unnamed: D3075.6 (CKO), D3076.4 (CKI)
unnamed: D3075.1 (SDO), D3076.3 (SDI)
unnamed: D3076.6 (CKO), D3077.4 (CKI)
unnamed: D3076.1 (SDO), D3077.3 (SDI)
unnamed: D3077.6 (CKO), D3078.4 (CKI)
unnamed: D3077.1 (SDO), D3078.3 (SDI)
unnamed: D3078.6 (CKO), D3079.4 (CKI)
unnamed: D3078.1 (SDO), D3079.3 (SDI)
unnamed: D3079.6 (CKO), D3080.4 (CKI)
unnamed: D3079.1 (SDO), D3080.3 (SDI)
unnamed: D3081.6 (CKO), D3082.4 (CKI)
unnamed: D3081.1 (SDO), D3082.3 (SDI)
unnamed: D3082.6 (CKO), D3083.4 (CKI)
unnamed: D3082.1 (SDO), D3083.3 (SDI)
unnamed: D3083.6 (CKO), D3084.4 (CKI)
unnamed: D3083.1 (SDO), D3084.3 (SDI)
unnamed: D3084.6 (CKO), D3085.4 (CKI)
unnamed: D3084.1 (SDO), D3085.3 (SDI)
unnamed: D3085.6 (CKO), D3086.4 (CKI)
unnamed: D3085.1 (SDO), D3086.3 (SDI)
unnamed: D3086.6 (CKO), D3087.4 (CKI)
unnamed: D3086.1 (SDO), D3087.3 (SDI)
unnamed: D3087.6 (CKO), D3088.4 (CKI)
unnamed: D3087.1 (SDO), D3088.3 (SDI)
unnamed: D3089.6 (CKO), D3090.4 (CKI)
unnamed: D3089.1 (SDO), D3090.3 (SDI)
unnamed: D3090.6 (CKO), D3091.4 (CKI)
unnamed: D3090.1 (SDO), D3091.3 (SDI)
unnamed: D3091.6 (CKO), D3092.4 (CKI)
unnamed: D3091.1 (SDO), D3092.3 (SDI)
unnamed: D3092.6 (CKO), D3093.4 (CKI)
unnamed: D3092.1 (SDO), D3093.3 (SDI)
unnamed: D3093.6 (CKO), D3094.4 (CKI)
unnamed: D3093.1 (SDO), D3094.3 (SDI)
unnamed: D3094.6 (CKO), D3095.4 (CKI)
unnamed: D3094.1 (SDO), D3095.3 (SDI)
unnamed: D3095.6 (CKO), D3096.4 (CKI)
unnamed: D3095.1 (SDO), D3096.3 (SDI)
unnamed: D3097.6 (CKO), D3098.4 (CKI)
unnamed: D3097.1 (SDO), D3098.3 (SDI)
unnamed: D3098.6 (CKO), D3099.4 (CKI)
unnamed: D3098.1 (SDO), D3099.3 (SDI)
unnamed: D3099.6 (CKO), D3100.4 (CKI)
unnamed: D3099.1 (SDO), D3100.3 (SDI)
unnamed: D3100.6 (CKO), D3101.4 (CKI)
unnamed: D3100.1 (SDO), D3101.3 (SDI)
unnamed: D3101.6 (CKO), D3102.4 (CKI)
unnamed: D3101.1 (SDO), D3102.3 (SDI)
unnamed: D3102.6 (CKO), D3103.4 (CKI)
unnamed: D3102.1 (SDO), D3103.3 (SDI)
unnamed: D3103.6 (CKO), D3104.4 (CKI)
unnamed: D3103.1 (SDO), D3104.3 (SDI)
unnamed: D3105.6 (CKO), D3106.4 (CKI)
unnamed: D3105.1 (SDO), D3106.3 (SDI)
unnamed: D3106.6 (CKO), D3107.4 (CKI)
unnamed: D3106.1 (SDO), D3107.3 (SDI)
unnamed: D3107.6 (CKO), D3108.4 (CKI)
unnamed: D3107.1 (SDO), D3108.3 (SDI)
unnamed: D3108.6 (CKO), D3109.4 (CKI)
unnamed: D3108.1 (SDO), D3109.3 (SDI)
unnamed: D3109.6 (CKO), D3110.4 (CKI)
unnamed: D3109.1 (SDO), D3110.3 (SDI)
unnamed: D3110.6 (CKO), D3111.4 (CKI)
unnamed: D3110.1 (SDO), D3111.3 (SDI)
unnamed: D3111.6 (CKO), D3112.4 (CKI)
unnamed: D3111.1 (SDO), D3112.3 (SDI)
unnamed: D3113.6 (CKO), D3114.4 (CKI)
unnamed: D3113.1 (SDO), D3114.3 (SDI)
unnamed: D3114.6 (CKO), D3115.4 (CKI)
unnamed: D3114.1 (SDO), D3115.3 (SDI)
unnamed: D3115.6 (CKO), D3116.4 (CKI)
unnamed: D3115.1 (SDO), D3116.3 (SDI)
unnamed: D3116.6 (CKO), D3117.4 (CKI)
unnamed: D3116.1 (SDO), D3117.3 (SDI)
unnamed: D3117.6 (CKO), D3118.4 (CKI)
unnamed: D3117.1 (SDO), D3118.3 (SDI)
unnamed: D3118.6 (CKO), D3119.4 (CKI)
unnamed: D3118.1 (SDO), D3119.3 (SDI)
unnamed: D3119.6 (CKO), D3120.4 (CKI)
unnamed: D3119.1 (SDO), D3120.3 (SDI)
unnamed: D3121.6 (CKO), D3122.4 (CKI)
unnamed: D3121.1 (SDO), D3122.3 (SDI)
unnamed: D3122.6 (CKO), D3123.4 (CKI)
unnamed: D3122.1 (SDO), D3123.3 (SDI)
unnamed: D3123.6 (CKO), D3124.4 (CKI)
unnamed: D3123.1 (SDO), D3124.3 (SDI)
unnamed: D3124.6 (CKO), D3125.4 (CKI)
unnamed: D3124.1 (SDO), D3125.3 (SDI)
unnamed: D3125.6 (CKO), D3126.4 (CKI)
unnamed: D3125.1 (SDO), D3126.3 (SDI)
unnamed: D3126.6 (CKO), D3127.4 (CKI)
unnamed: D3126.1 (SDO), D3127.3 (SDI)
unnamed: D3127.6 (CKO), D3128.4 (CKI)
unnamed: D3127.1 (SDO), D3128.3 (SDI)
VLED: C3001.1, C3002.1, C3003.1, C3004.1, C3005.1, C3006.1, C3007.1, C3008.1, C3009.1, C3010.1, C3011.1, C3012.1, C3013.1, C3014.1, C3015.1, C3016.1, C3017.1, C3018.1, C3019.1, C3020.1, C3021.1, C3022.1, C3023.1, C3024.1, C3025.1, C3026.1, C3027.1, C3028.1, C3029.1, D3001.5 (VDD), D3002.5 (VDD), D3003.5 (VDD), D3004.5 (VDD), D3005.5 (VDD), D3006.5 (VDD), D3007.5 (VDD), D3008.5 (VDD), D3009.5 (VDD), D3010.5 (VDD), D3011.5 (VDD), D3012.5 (VDD), D3013.5 (VDD), D3014.5 (VDD), D3015.5 (VDD), D3016.5 (VDD), D3017.5 (VDD), D3018.5 (VDD), D3019.5 (VDD), D3020.5 (VDD), D3021.5 (VDD), D3022.5 (VDD), D3023.5 (VDD), D3024.5 (VDD), D3025.5 (VDD), D3026.5 (VDD), D3027.5 (VDD), D3028.5 (VDD), D3029.5 (VDD), D3030.5 (VDD), D3031.5 (VDD), D3032.5 (VDD), D3033.5 (VDD), D3034.5 (VDD), D3035.5 (VDD), D3036.5 (VDD), D3037.5 (VDD), D3038.5 (VDD), D3039.5 (VDD), D3040.5 (VDD), D3041.5 (VDD), D3042.5 (VDD), D3043.5 (VDD), D3044.5 (VDD), D3045.5 (VDD), D3046.5 (VDD), D3047.5 (VDD), D3048.5 (VDD), D3049.5 (VDD), D3050.5 (VDD), D3051.5 (VDD), D3052.5 (VDD), D3053.5 (VDD), D3054.5 (VDD), D3055.5 (VDD), D3056.5 (VDD), D3057.5 (VDD), D3058.5 (VDD), D3059.5 (VDD), D3060.5 (VDD), D3061.5 (VDD), D3062.5 (VDD), D3063.5 (VDD), D3064.5 (VDD), D3065.5 (VDD), D3066.5 (VDD), D3067.5 (VDD), D3068.5 (VDD), D3069.5 (VDD), D3070.5 (VDD), D3071.5 (VDD), D3072.5 (VDD), D3073.5 (VDD), D3074.5 (VDD), D3075.5 (VDD), D3076.5 (VDD), D3077.5 (VDD), D3078.5 (VDD), D3079.5 (VDD), D3080.5 (VDD), D3081.5 (VDD), D3082.5 (VDD), D3083.5 (VDD), D3084.5 (VDD), D3085.5 (VDD), D3086.5 (VDD), D3087.5 (VDD), D3088.5 (VDD), D3089.5 (VDD), D3090.5 (VDD), D3091.5 (VDD), D3092.5 (VDD), D3093.5 (VDD), D3094.5 (VDD), D3095.5 (VDD), D3096.5 (VDD), D3097.5 (VDD), D3098.5 (VDD), D3099.5 (VDD), D3100.5 (VDD), D3101.5 (VDD), D3102.5 (VDD), D3103.5 (VDD), D3104.5 (VDD), D3105.5 (VDD), D3106.5 (VDD), D3107.5 (VDD), D3108.5 (VDD), D3109.5 (VDD), D3110.5 (VDD), D3111.5 (VDD), D3112.5 (VDD), D3113.5 (VDD), D3114.5 (VDD), D3115.5 (VDD), D3116.5 (VDD), D3117.5 (VDD), D3118.5 (VDD), D3119.5 (VDD), D3120.5 (VDD), D3121.5 (VDD), D3122.5 (VDD), D3123.5 (VDD), D3124.5 (VDD), D3125.5 (VDD), D3126.5 (VDD), D3127.5 (VDD), D3128.5 (VDD), J1.3; also elsewhere on the board

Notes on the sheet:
10u 10V X5R/X7R MLCCs in parallel
470u 10V low ESR aluminum polymer
